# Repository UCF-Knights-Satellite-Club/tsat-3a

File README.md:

# TSat-3A
Electrical and software development repository for TSat-3A, containing KiCad schematics, Arduino firmware, Processing visualizations, and supporting development files for the mission's electrical subsystems.

## Documentation
Public project documentation can be found on the [KSC Wiki](https://wiki.kscucf.org/projects/tethered-satellite/tsat-3).

## License

- Software (`sim/`, `Arduino/`, `Processing/`, and the Python generator and check scripts in the `PCBMotor*/` folders): [MIT](LICENSE)
- Hardware designs (the KiCad files in `PCBMotorTest/`, `PCBMotorStrandTest/`, `PCBMotorWaveTest/`): [CERN Open Hardware Licence v2, Permissive (CERN-OHL-P-2.0)](LICENSE-HARDWARE)

Copyright (c) 2026 Knights Satellite Club

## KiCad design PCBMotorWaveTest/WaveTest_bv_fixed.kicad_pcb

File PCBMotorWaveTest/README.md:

# PCB motor wave-winding test stators (v0.1)

Three 4-layer stators (plus blind-via versions of the same three, `bv_*`, described below) that test the wave winding the sim now recommends for the payload. They are
`sim/results/pcbmotor_wave.md` and RESULTS.md 5f, built for the same rotor as the strand-test boards.
The three boards differ only in their copper:

| Board | Winding | What it measures |
|---|---|---|
| `WaveTest_solid` | one trace per conductor, width ≤ 1.2 mm | baseline Kt, R and eddy drag of the wave winding |
| `WaveTest_swap` | two strands per conductor (≤ 1.6 mm in all), lanes **swapped** at every outer via | the recommended winding: lower eddy drag, no strand circulating current |
| `WaveTest_fixed` | the same two strands, lanes **fixed** | the circulating current that the swap cancels |

`swap` and `fixed` have identical copper apart from where the strands cross at the outer vias. Their
difference in coast-down drag is the strand circulating current, which every paper in `~/KSC/research`
flags as the failure mode of paralleled PCB traces.

## Files

| File | What it is |
|---|---|
| `WaveTest_<variant>.kicad_pro` / `.kicad_pcb` | The boards. Open the `.kicad_pro` in KiCad 10. |
| `gen_wave_test.py` | Draws the boards from `sim/pcbmotor/wave_layout.py` (system Python, has `pcbnew`). |
| `wavetest_<variant>_asbuilt.json` | Layout summary: radii, jumpers, the loop chain of each phase, and the sim's checks. |
| `renders/` | 3D renders from `kicad-cli`. |

The copper is built in `sim/pcbmotor/wave_layout.py`, which also checks it. `sim/pcbmotor/wave_asbuilt.py`
runs the EM model on exactly that copper and writes `sim/results/pcbmotor_wave_asbuilt.json`.

## Regenerate and check

```bash
python3 PCBMotorWaveTest/gen_wave_test.py                 # all three boards (system Python, has pcbnew)
for v in solid swap fixed; do
  kicad-cli pcb drc --severity-error PCBMotorWaveTest/WaveTest_$v.kicad_pcb
  python3 PCBMotorTest/check_spacing.py PCBMotorWaveTest/WaveTest_$v.kicad_pcb --space 0.15
done
cd sim && .venv/bin/python tests/test_wave_layout.py && .venv/bin/python -m pcbmotor.wave_asbuilt
```

The generator refuses to write a board unless the sim's checks pass:
- each phase is one series path through all 64 of its conductors, with the current outward on every
  + conductor;
- no shorts between phases;
- every copper gap is at least 0.15 mm.

As generated (2026-11-19), all three boards have 0 DRC errors, 0 unconnected items, and 0 net-blind
spacing violations at 0.15 mm on every layer. `check_spacing.py` was extended for these boards: it now
joins tracks that meet end to end into one piece of copper, so a curve drawn as short segments isn't
mistaken for overlapping copper. It also gained `--dump file.csv`. `PCBMotorTest` and both
`PCBMotorStrandTest` boards still pass it.

The generator overwrites the boards. Once you edit one in the KiCad GUI, either keep using the script
(change `wave_layout.py` and regenerate) or switch to editing by hand, not both.

## Design

| | |
|---|---|
| Fab | JLCPCB 4-layer, 1.6 mm, 2 oz copper on all four layers (`jlc4_2oz`, the same as the strand-test boards). The stackup is JLC's published one: 70 / 61 / 61 / 70 µm copper, 0.436 mm prepreg, 0.5 mm core, 1.63 mm finished. |
| Board | About 129 × 129 mm. M3 centre hole, four M3 hub holes on a 23 mm circle, four M3 corner holes. |
| Winding | 48 conductor positions per layer, 8 poles, q = 2 conductors per pole per phase, full pitch. Two layer pairs, each a two-layer wave: L1 + L2 and L3 + L4. All 4 layers are in series, 64 conductors per phase. |
| Radial (active) sections | pair 1: r 17.3 to 46.4 mm; pair 2: r 22 to 40 mm. The magnets cover 21.5 to 40.5 mm. |
| Via rings | pair 1: r 14.5 and 51.0 mm; pair 2: r 18.6 and 44.6 mm. 0.3 mm drill, 0.56 mm pad. |
| Strands | Two lanes from the start of the active section (r 22 mm) to the outer via. They merge into one solid trace at the inner end. |
| Phase pads | Six THT wire pads, A1/A2, B1/B2, C1/C2, at r about 59 mm. Each phase is the winding between its two pads. Wire star or delta off the board. |
| Rotor (not drawn) | The payload rotor: 8 × 19.05 × 12.7 × 6.35 mm N42 blocks at r 31 mm on an 84 × 1.5 mm steel disc, 0.6 mm air gap. The magnets are on F.Fab. |

**Layout.** Each conductor runs radially across the magnets, then slants half a pole pitch to a via
ring at each end. A top conductor (L1 or L3) and the bottom conductor a pole pitch further round (L2 or
L4) share an outer via. That bottom conductor and the next top conductor share an inner via, and so on
round the board. That is a full-pitch wave, with nothing crossing on any layer.

**Why the two pairs are nested.** Through vias pierce all four layers, and a pair's slanted end turns
are packed too tightly to let the other pair's via through. So pair 2's vias sit on rings at 18.6 and
44.6 mm. Pair 1 runs straight past them, exactly midway between them (it sits half a slot round from
pair 2), and only then slants to its own rings at 14.5 and 51.0 mm.

**The strand swap is just via placement.** At an outer via, the top conductor's lanes and the bottom
conductor's lanes meet where they cross.
- `swap` pairs each lane with the opposite lane. The two crossings stack radially at the via's angle,
  so each strand spends one conductor on each side.
- `fixed` pairs each lane with the same lane. The crossings sit side by side on the ring.

The strands merge at the inner end, so each top + bottom conductor pair is one strand loop. With the
swap, each strand in that loop links the same flux to first order.

**Loops, breaks and jumpers.** With every via in place, each phase forms 8 closed wave loops:
2 pairs × 2 slots × 2 pole parities. Each loop is opened at one outer via near its phase's cluster
(A at ~10°, B at ~130°, C at ~250°).
- At each break the lanes fan out to a root 1.2 mm beyond the ring. A stub runs on to a terminal via
  at r ≈ 53.8 mm.
- Jumpers chain the loops in series. Each is a radial lead on F.Cu and an arc on In1.Cu and In2.Cu in
  parallel, on rings at 55.3 and 56.5 mm.
- The first and last loop ends run out on B.Cu to the phase pads.

## Predictions (as built, `sim/pcbmotor/wave_asbuilt.py`, JLC's published stackup since 2026-11-23)

| | Kt mN·m/A | R phase Ω | Km mN·m/√W | Eddy drag @2000 rpm | Strand circulating @2000 rpm | Total drag @2000 rpm |
|---|---|---|---|---|---|---|
| solid | 22.5 | 0.95 | 18.9 | 0.36 W | – | **1.71 mN·m** |
| swap | 22.5 | 0.91 | 19.2 | 0.16 W | 0.002 W | **0.77 mN·m** |
| fixed | 22.5 | 0.91 | 19.2 | 0.16 W | 0.17 W | **1.59 mN·m** |

Drag grows linearly with speed: at 3000 rpm it is 2.6, 1.2 and 2.4 mN·m.

- **swap vs solid:** stranding halves the eddy drag.
- **fixed vs swap:** the about 0.8 mN·m difference is the circulating current alone.

Phase resistance includes about 0.1 Ω of jumpers, stubs and vias. Plan on a 5–15% torque derating
before trusting Kt to better than that: Paul et al. 2019 measured a wave PCB motor 15.5% below FEA.

## Blind-via boards (`WaveTest_bv_*`, 2026-11-19)

`bv_solid`, `bv_swap` and `bv_fixed` are the same three windings built with **blind vias**. Pair 1's
vias span only L1–L2 (from the top) and pair 2's only L3–L4 (from the bottom). A via then no longer
blocks the other pair's copper, so the two pairs share via rings at 18.6 and 44.6 mm, and pair 1 no
longer runs the long way round pair 2's rings.
- The terminal and jumper vias outside the winding stay through vias.
- `wave_layout.py`: `WaveLayoutParams(buried=True)`. Vias carry their layer span, and the
  connectivity and spacing checks only count a via on the layers it reaches. `check_spacing.py` now
  does the same.
- All three boards are DRC clean, fully connected and pass the net-blind spacing check.

| As built, at 15 mN·m and 2000 rpm | Km mN·m/√W | R phase Ω | Loss | Drag (swap / fixed) |
|---|---|---|---|---|
| Through vias, 2 oz (this folder's main boards), swap | 19.2 | 0.91 | 0.77 W | 0.77 / 1.59 mN·m |
| Blind vias, 2 oz, swap | 20.6 | 0.81 | 0.69 W | 0.76 / 1.68 mN·m |
| Blind vias, 3 oz (ASSUMED ACE-style build, 0.2 mm space, 0.4 / 0.2 mm vias), swap | 23.6 | 0.61 | 0.64 W | 1.13 / 2.56 mN·m |
| Spiral coils (the current payload design), for reference | 16.2 | 1.21 | 1.75 W | – |

Kt is about 22.5 mN·m/A for all of them. With heavier copper the strand lanes narrow to 0.30 mm, so
0.56 mm vias no longer fit: 3 oz needs vias of 0.4 mm pad or smaller. Laser blind vias in an HDI build
are about 0.1 / 0.3 mm.

**Board size.** Blind vias bring the copper's outer edge in from r ≈ 51.7 mm to ≈ 45.4 mm. But the
loop breaks, jumper rings and phase pads still sit outside the winding, so the board is still about
117 mm square. **Blind vias alone don't fit the 90 mm payload.** What would:
- a 6-layer build with two layers just for the jumpers (L1–L2 pair 1, L3–L4 jumpers, L5–L6 pair 2);
- breaks taken at the inner via ring, with the jumper arcs running under the winding on the jumper
  layers and the phase leads running out to pads in the board corners.

That needs blind vias spanning L1–L3 and L4–L6 as well as L1–L2 and L5–L6. It hasn't been laid out yet.

**Fab questions:**
- JLC's HDI service lists laser blind vias on 4–24 layers, but whether it allows 2 oz copper with
  them isn't checked. Laser vias need about 1:1 aspect ratio, so a thin L1–L2 and L3–L4 dielectric.
- ACE lists blind/buried vias, sequential lamination and 3 oz inner copper. Ask whether these combine,
  and at what spacing.

## Bench tests (same rig and rotor as the strand-test boards)

1. DC resistance of each phase, cold, with board temperature logged. Compare with R above.
2. Back-EMF at a known speed (spin the rotor with a drill or the strand-test rig). Peak phase EMF per
   rad/s = 2/3 × Kt.
3. Coast-down from about 3000 rpm with the phase pads open: measure the drag torque for each board, then
   for a plain FR-4 blank to separate the bearing and windage drag. Expect solid ≈ fixed > swap.
4. Optional: static torque at 1 A with the rotor locked (Kt directly).

## Open items

- **Rotor and rig.** These need the same rotor and spin rig as the strand-test boards. That is Murilo's
  rotor review task in Notion.
- **Board size (through-via boards).** The nested via rings push pair 1's outer vias to r = 51 mm, and the jumpers and pads
  out to about 59 mm, so this board is about 129 mm square. **This layout does not fit the 90 × 90 mm
  payload.** Options for the payload:
  - blind vias: modelled in the `bv_*` boards. They shrink the winding, but not enough on their own (see above);
  - solid traces only (no strands, so the via ends can be steeper and shorter);
  - a smaller active band, at some cost in Kt;
  - a 6-layer board with the jumpers on their own layers.
- **Break conductors.** The 8 conductor pairs per phase that hold a loop break merge their strands
  without a swap. The model treats them like the rest, which slightly underestimates `swap`'s
  circulating current.
- **JLC confirmation.** Check that a 0.3 mm drill with a 0.56 mm via pad (0.13 mm annular ring) is
  accepted on 2 oz copper. The strand-test boards use 0.6 mm pads.

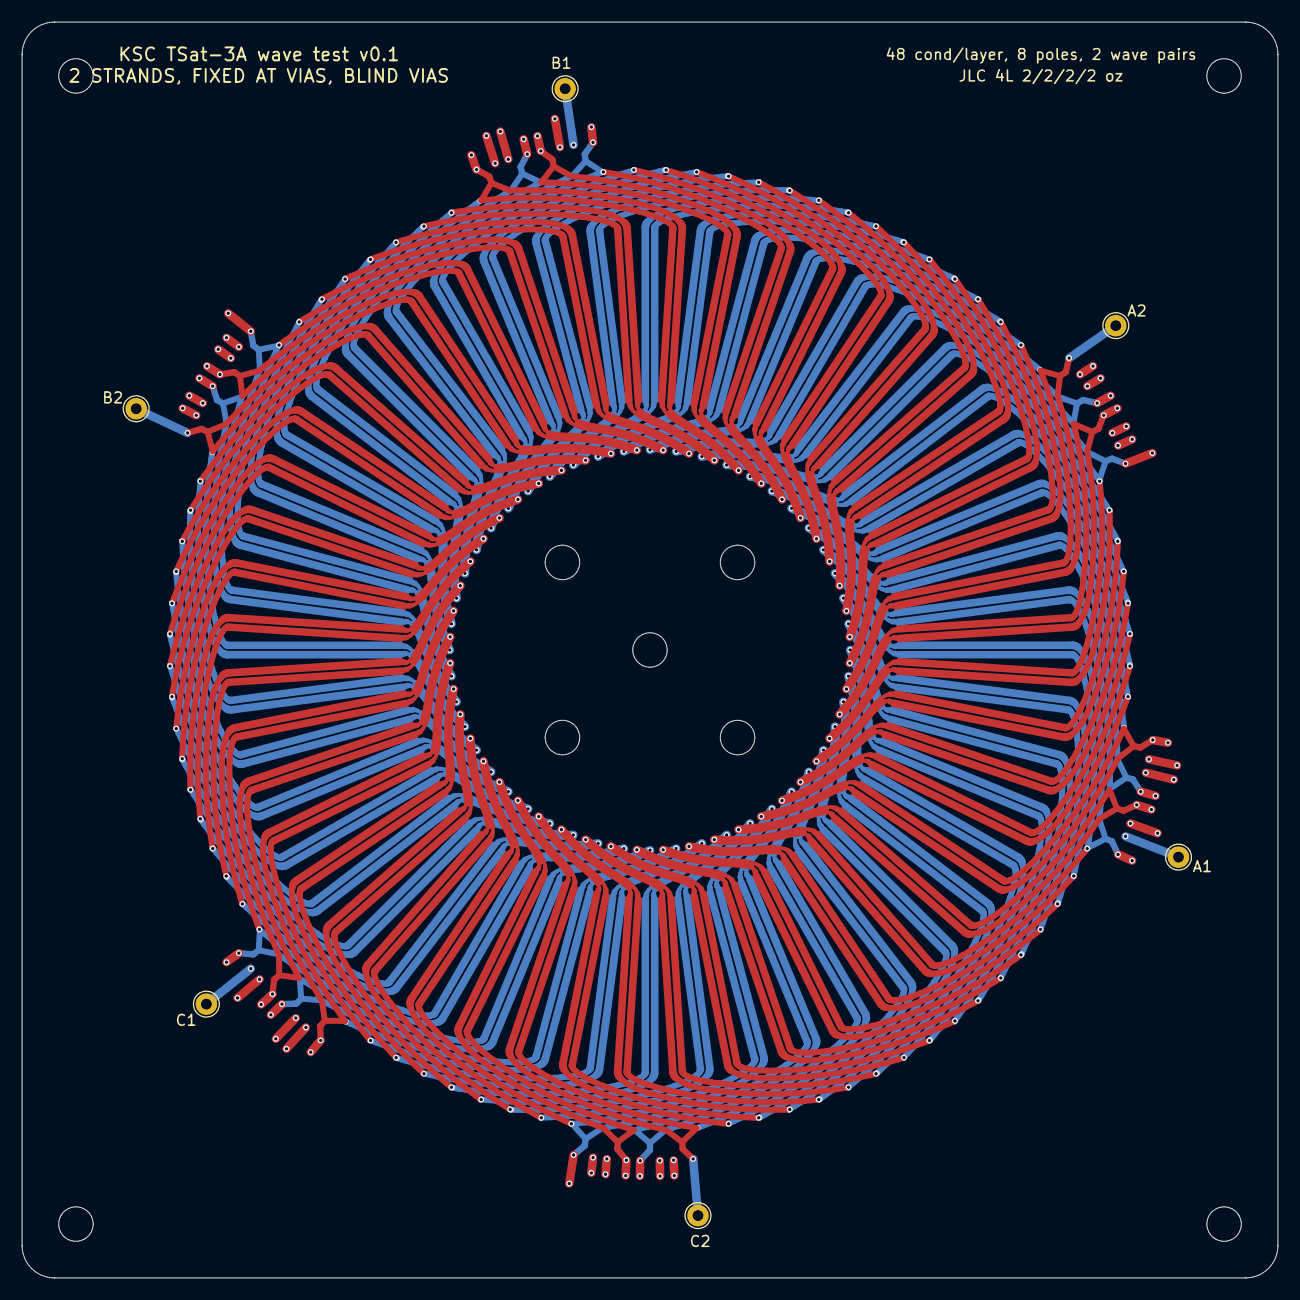
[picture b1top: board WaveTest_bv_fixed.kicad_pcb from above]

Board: 4 copper layers, 116.6 x 116.6 mm, 15 parts (0 on the bottom side), 3 nets.

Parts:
A1: A1; TestPoint_THTPad_D2.0mm_Drill1.0mm
A2: A2; TestPoint_THTPad_D2.0mm_Drill1.0mm
B1: B1; TestPoint_THTPad_D2.0mm_Drill1.0mm
B2: B2; TestPoint_THTPad_D2.0mm_Drill1.0mm
C1: C1; TestPoint_THTPad_D2.0mm_Drill1.0mm
C2: C2; TestPoint_THTPad_D2.0mm_Drill1.0mm
H1: Axle M3; MountingHole_3.2mm_M3
H2, H3, H4, H5: Hub M3; MountingHole_3.2mm_M3
H6, H7, H8, H9: M3; MountingHole_3.2mm_M3

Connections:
PHASE_A: A1.1, A2.1
PHASE_B: B1.1, B2.1
PHASE_C: C1.1, C2.1

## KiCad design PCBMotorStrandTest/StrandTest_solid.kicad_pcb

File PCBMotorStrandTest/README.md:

# PCB motor strand test: solid vs stranded stators (v0.1)

Two 4-layer stators that are identical except for the coil copper. One winds a solid 1.2 mm trace.
The other winds the same 1.2 mm as three 0.30 mm strands, transposed at the layer vias ("PCB Litz").
Spinning the same rotor over each board measures how much eddy drag the strands remove. Today that
number only exists in the model (`sim/pcbmotor/ace_stackups.py`, `cubesat_wheels.py`,
`large_wheels.py` all assume stranded windings). This board tests it.

## Why the payload geometry, not the small test stator

Eddy loss goes with trace width squared. On the 40 mm test stator the 0.15 mm traces lose almost
nothing, and even 1 mm traces with its small magnets give about 0.16 mN·m at 3,000 rpm. Bearing
drag would swamp that. These boards are the recommended high-momentum payload stator
(`payload_high_momentum` in `sim/results/pcbmotor_designs.json`) and run the payload rotor. They're
built on JLC's all-2 oz 4-layer board, the best JLC option in `sim/results/pcbmotor_ace_stackups.md`.
The payload design itself is 2 oz outer / 1 oz inner. The solid board loses about 7.3 mN·m at
3,000 rpm, so the difference is easy to measure, and the result checks the payload board directly.

## Files

| File | What it is |
|---|---|
| `StrandTest_solid.kicad_pro` / `.kicad_pcb` | Solid board. Open the `.kicad_pro` in KiCad 10. |
| `StrandTest_stranded.kicad_pro` / `.kicad_pcb` | Stranded board. |
| `gen_strand_test.py` | Generates both boards from the sim's design and `sim/pcbmotor/bundle.py`. |
| `strandtest_<variant>_asbuilt.json` | Turns, lane lengths, ring track lengths, J2 pad-to-strand map. `sim/pcbmotor/strand_test.py` reads them. |
| `renders/` | 3D renders from `kicad-cli`. |

The copper is built in `sim/pcbmotor/bundle.py`, and the solid board is the same code with one
strand. The predictions come from `sim/pcbmotor/strand_test.py` and are written to
`sim/results/pcbmotor_strand_test.md`.

## Regenerate and check

```bash
python3 PCBMotorStrandTest/gen_strand_test.py                     # both boards (system Python, has pcbnew)
kicad-cli pcb drc --severity-error PCBMotorStrandTest/StrandTest_solid.kicad_pcb
kicad-cli pcb drc --severity-error PCBMotorStrandTest/StrandTest_stranded.kicad_pcb
python3 PCBMotorTest/check_spacing.py PCBMotorStrandTest/StrandTest_solid.kicad_pcb --space 0.15
python3 PCBMotorTest/check_spacing.py PCBMotorStrandTest/StrandTest_stranded.kicad_pcb --space 0.15
cd sim && .venv/bin/python tests/test_bundle.py && .venv/bin/python -m pcbmotor.strand_test
```

The generator overwrites both boards. Once you start editing one in the KiCad GUI, either keep
using the script (change its parameters and regenerate) or switch to editing by hand, not both.

## Design

| | |
|---|---|
| Fab | JLCPCB 4-layer, 1.6 mm, 2 oz copper on all four layers (`jlc4_2oz`, set by `STRAND_TEST_STACKUP` in `sim/pcbmotor/bundle.py`). JLC only offers 2 oz inner copper on 4-layer 1.6 mm boards with 2 oz outer. The stackup in the file is JLC's published one: 70 / 61 / 61 / 70 µm copper, 0.436 mm prepreg, 0.5 mm core, 1.63 mm finished. |
| Board | 100 × 100 mm. Four M3 corner holes, an M3 centre hole, and four M3 holes on a 24 mm circle for a bearing housing. |
| Winding | 6 coils / 8 poles, 21–41 mm radius, 1.2 mm bundle / 0.15 mm space, 7 turns per layer, 4 layers in series per coil, two coils in series per phase |
| Solid | one 1.2 mm trace |
| Stranded | three 0.30 mm strands, 0.15 mm apart (JLC's 2 oz minimum) |
| Vias | 0.3 mm drill / 0.6 mm pad, one per strand at each layer change |
| Ring | Phase wiring arcs on In1 and In2 in parallel, 0.9 mm wide, outside the winding at 43.6–46.9 mm radius |
| Header J1 (bottom, 2.54 mm) | 1 B1, 2 A2, 3 C2, 4 B2, 5 A1, 6 C1, the same as the test stator. For star, tie A2 + B2 + C2. |
| Rotor (not drawn) | payload rotor: 8 × 19.05 × 12.7 × 6.35 mm N42 blocks at 31 mm radius on an 84 × 1.5 mm steel disc, 0.6 mm air gap. The F.Fab layer shows the magnets. |

**How the strands are wound.** Each turn is a bundle of three lanes that fills the solid trace's
width, so both boards have the same turns and the same current centroid (Kt 20.1 mN·m/A on both).
The strands only join at the coil terminals. On L1 they start from a short bus arc outside the
winding, and on L4 they end on another.

**Transposition.** With only through vias and radial stubs, the lane next to the coil opening has
to leave a layer first, so every via set reverses the lane order. A strand runs lane s on L1,
n−1−s on L2, s on L3 and n−1−s on L4. Over the four layers every strand links almost the same
flux. Without that, a current would circulate round the strand loop at speed. The model puts the
untransposed version at 0.33 mN·m at 3,000 rpm, nearly doubling the stranded board's drag. With the
transposition it's 0.2 % of the drag.

**Vias.** For the payload geometry the coil opening is a wide, shallow slot, about 1.1 mm of
clear space between the last turns. The L1→L2 and L3→L4 vias sit side by side in a row across it.
The L2→L3 vias sit just outside the winding on the coil axis. On the solid board the 1.2 mm trace
necks down to 0.6 mm for the last stub into each via, so its round end doesn't reach the next turn.

**J2 (stranded board only).** On coil A+ (the right-hand A+), the three strands end on a 3-pad
solder jumper instead of a bus. The phase lead connects to pad 2, the middle strand. For normal
use, **bridge 1-2 and 2-3 with solder**. Left open, it lets you:
- check strand continuity and isolation: pad to pad reads two strands in series, 3.07 Ω;
- measure the strand-to-strand back-EMF directly with the rotor spinning. This is the quantity the
  transposition is meant to cancel.

J2 sits at 42.3 mm radius, outside the magnet corners (41.0 mm), so solder on it can't touch the
rotor.

## Checks done (2026-11-19)

- **KiCad DRC:** 0 errors and 0 unconnected on both boards.
- **`check_spacing.py` at 0.15 mm:** 0 violations on every layer of both boards. All strands of a
  phase are one net, so DRC never checks strand-to-strand gaps; this check does. Rerunning it at
  0.16 mm flags the strand gaps everywhere, which shows it sees them. It found a real problem on the
  first pass: the solid trace's round end reached past its via toward the next turn. That's why the
  via stubs neck down.
- **`sim/tests/test_bundle.py`:** strands are continuous through their vias, at least 0.15 mm apart
  inside the winding, every lane winds counter-clockwise, and every strand gets the same total lane
  offset.

`check_spacing.py` got one change for these boards. Along a single track, it now treats points
closer than the track's own width + space as the same copper. Before, a 1.2 mm trace flagged
itself. The 0.15 mm test stator still checks clean.

## What the boards should measure

From `sim/results/pcbmotor_strand_test.md` (JLC's published stackup, 2026-11-23). Drag is the stator's own, with the phases open. It
doesn't include bearing drag (see below).

| | Solid | Stranded |
|---|---|---|
| Phase resistance, 20 °C (A1–A2 / B1–B2 / C1–C2) | 0.82 / 0.84 / 0.83 Ω | 1.07 / 1.09 / 1.07 Ω |
| Kt (FOC, per A peak) | 20.1 mN·m/A | 20.1 mN·m/A |
| Phase back-EMF | 1.40 V peak per 1000 rpm (66.7 Hz electrical per 1000 rpm) | same |
| Stator drag at 1,000 / 2,000 / 3,000 rpm | 2.43 / 4.85 / 7.28 mN·m | 0.114 / 0.227 / 0.341 mN·m |
| Loss at 3,000 rpm | 2.29 W | 0.107 W |
| Extra deceleration at 3,000 rpm (rotor J = 2.04e-4 kg·m²) | 341 rpm/s | 16.0 rpm/s |

Drag ratio solid / stranded: **21×**. This matches the design-study estimate (21×), so a measured
ratio well below that means the strand model is missing something.

**J2 open** (stranded board): DC resistance pad to pad is 3.07 Ω, and phase A reads 2.11 Ω
instead of 1.07 Ω. With the rotor spinning, the open-circuit voltage between pads is 2.1–4.6 mV rms
per 1000 rpm, about 6–14 mV rms at 3,000 rpm. An untransposed bundle would show 36–74 mV rms per
1000 rpm. Measure it with a scope on AC coupling, triggered on a phase.

## Test procedure

1. **Baseline.** Spin the rotor on its bearing with no stator (an air-core stator puts no axial load
   on the bearing, so this is the same bearing load). Log the coast-down. That gives bearing + air
   drag against speed.
2. **Each board.** Spin the rotor up with the board itself as the motor, using any 3-phase FOC driver
   (for example SimpleFOC with an AS5048 on the axle). Then **disconnect the phases** and log the
   coast-down from the back-EMF: frequency gives speed, and a scope or ADC on A1–B1 is enough.
   Don't leave a powered-down driver connected: its MOSFET body diodes rectify the back-EMF and brake
   the rotor. A driver left powered with its bus above the back-EMF (7.3 V line peak at 3,000 rpm) is fine.
3. **Reduce.** Stator drag at speed ω is J × (deceleration with the board − deceleration without). Get
   J from the rotor's measured mass and dimensions, or from a spin-up at known current (J = Kt·I / α).
   The solid/stranded ratio doesn't depend on J.
4. **Also measure** phase R cold (4-wire, log the temperature: copper rises 0.39 %/K) and back-EMF
   amplitude. On the stranded board, measure the J2 pads before bridging.

The solid board's eddy loss is 2.6 W at 3,000 rpm. That's fine for a coast-down, but don't hold it
at speed for long.

## Ordering

Order both designs at JLCPCB: 4 layers, 1.6 mm, outer copper 2 oz, inner copper 2 oz, any colour.
Upload the Gerbers and drill files (`kicad-cli pcb export gerbers` / `kicad-cli pcb export drill`),
which aren't generated yet. Both boards fit in 100 × 100 mm. Get a quote: per the 2026-11-18 notes,
JLC pre-collects a 35 % DDP on PCBs for US individuals. OSH Park can't do 2 oz copper; its 4-layer
board (1.24 oz outer, 0.5 oz inner) would still compare solid against stranded, at about
$155 per design for three.

## Still open

- **Rotor and rig.** Nothing is drawn: the payload rotor disc and magnet carrier, the bearing housing
  on the four hub holes, and shims to set the 0.6 mm gap. Eight 19 mm N42 blocks on a steel disc pull
  hard: assemble with a jig.
- **Fab files.** Gerbers and drill files aren't exported yet.
- **JLC stackup.** Since 2026-11-23 the model and the board file use JLC's published all-2 oz stackup
  (70 µm outer, 61 µm inner copper, 0.436 mm prepreg, 0.5 mm core). Check that the order form's
  stackup matches.

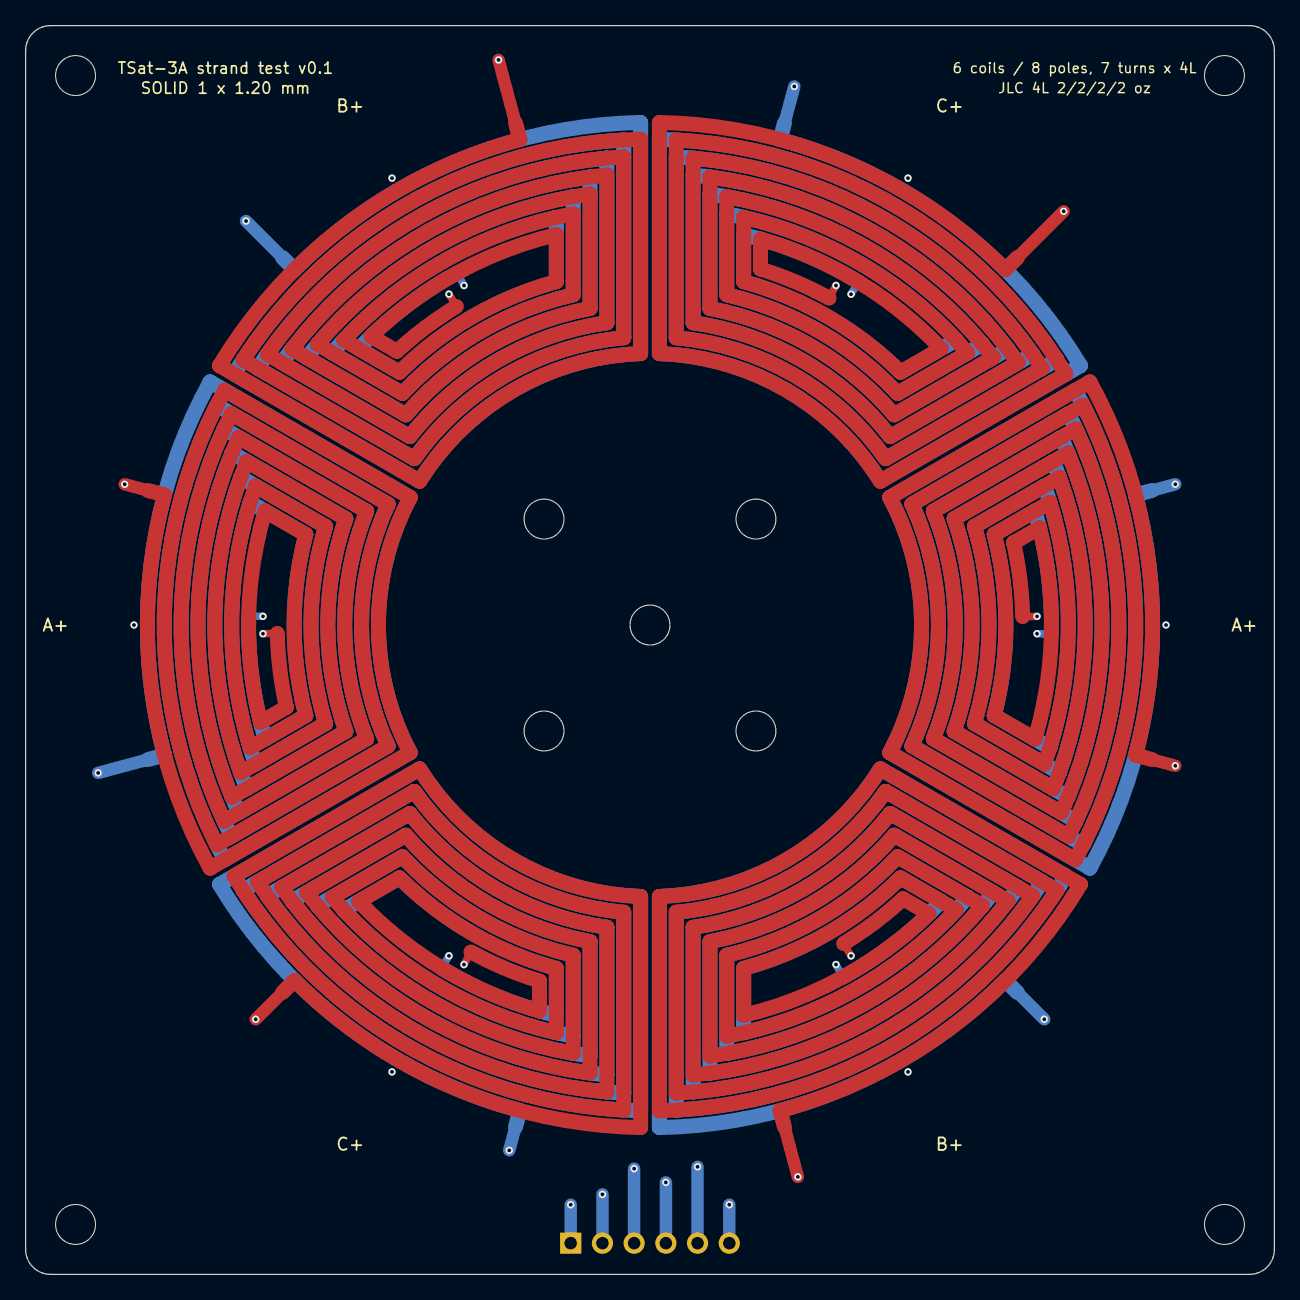
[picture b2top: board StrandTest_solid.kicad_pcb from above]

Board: 4 copper layers, 100.0 x 100.0 mm, 10 parts (1 on the bottom side), 3 nets.

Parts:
H1, H2, H3, H4: M3; MountingHole_3.2mm_M3
H5: Axle M3; MountingHole_3.2mm_M3
H6, H7, H8, H9: Hub M3; MountingHole_3.2mm_M3
J1: Phases; PinHeader_1x06_P2.54mm_Vertical

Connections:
PHASE_A: J1.2, J1.5
PHASE_B: J1.1, J1.4
PHASE_C: J1.3, J1.6

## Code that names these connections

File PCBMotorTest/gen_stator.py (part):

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        ("PHASE_A", (0, "E"), (3, "S"), True, 0),          # A: coil 0 -> coil 3
        ("PHASE_C", (1, "E"), (4, "S"), True, 1),          # C: coil 1 -> coil 4
        ("PHASE_B", (2, "E"), (5, "S"), False, 2),         # B: coil 2 -> coil 5 (clockwise, via 0 deg)
        ("PHASE_B", (2, "S"), ("pin", "B1"), True, 3),
        ("PHASE_A", (3, "E"), ("pin", "A2"), True, 2),
        ("PHASE_C", (4, "E"), ("pin", "C2"), True, 0),
        ("PHASE_B", (5, "E"), ("pin", "B2"), False, 1),
        ("PHASE_A", (0, "S"), ("pin", "A1"), False, 0),
        ("PHASE_C", (1, "S"), ("pin", "C1"), False, 3),
    ]
    ring_len = {n: {"outer_mm": 0.0, "inner_mm": 0.0, "vias": 0} for n in ("PHASE_A", "PHASE_B", "PHASE_C")}
    for net, src, dst, ccw, slot in routes:
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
